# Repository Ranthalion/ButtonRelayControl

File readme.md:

# Button Relay Control

Controls 2 relays based on liquid level sensors and push buttons

Video demo and more images at https://imgur.com/a/c6JBYJK

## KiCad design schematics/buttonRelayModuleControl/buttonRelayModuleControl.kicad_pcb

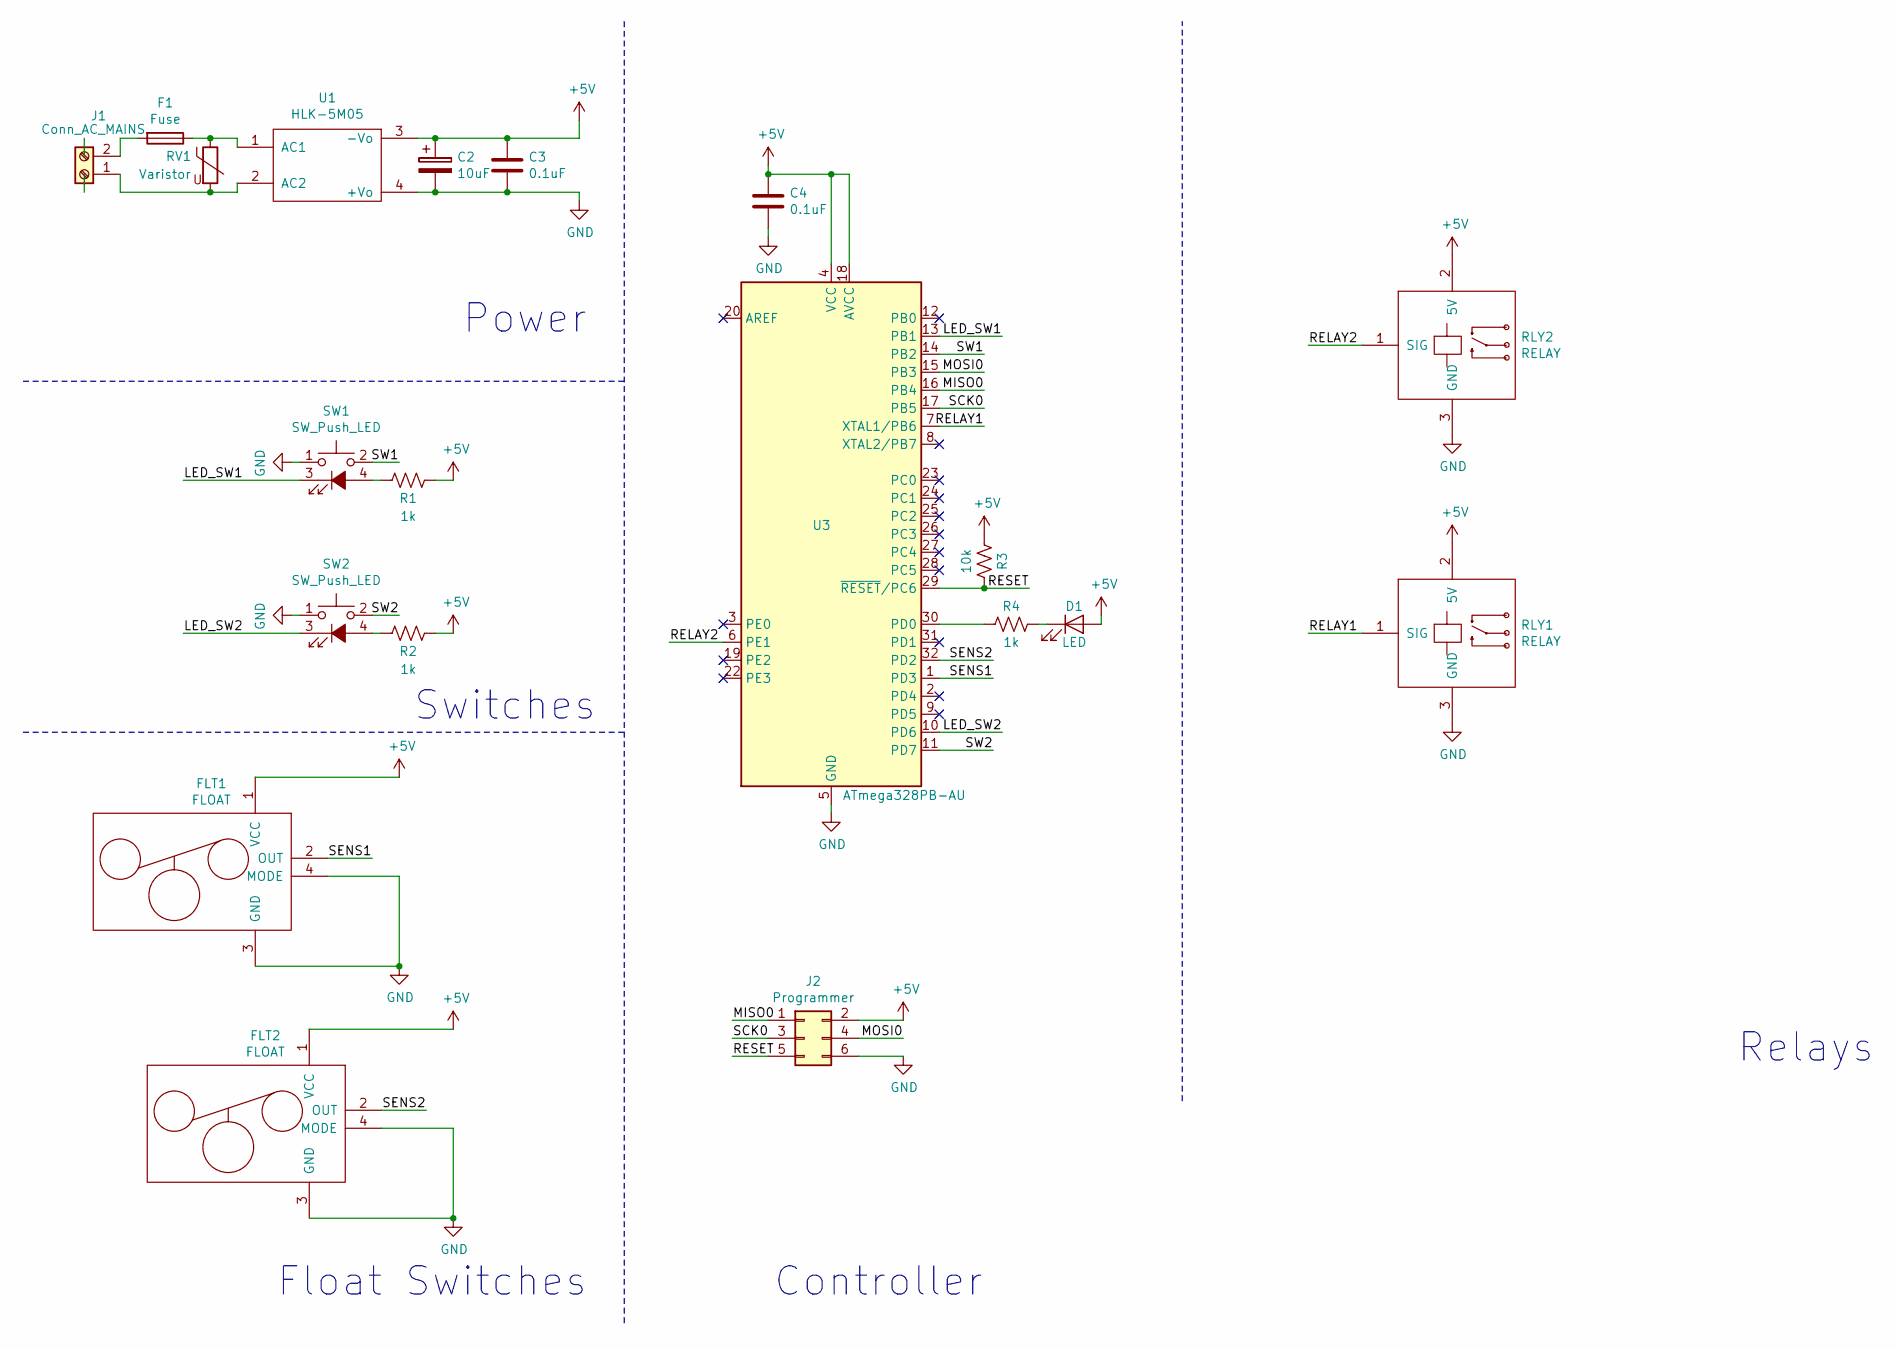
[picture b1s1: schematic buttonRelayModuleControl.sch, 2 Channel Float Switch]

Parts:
C2: 10uF; CP_Radial_D4.0mm_P1.50mm
C3, C4: 0.1uF; C_1206_3216Metric_Pad1.42x1.75mm_HandSolder
D1: LED; LED_0603_1608Metric_Pad1.05x0.95mm_HandSolder
F1: Fuse; Fuse_Bourns_MF-RG300; Part No 0466.125NR
FLT1, FLT2: FLOAT; JST_XH_B04B-XH-A_1x04_P2.50mm_Vertical
J1: Conn_AC_MAINS; Molex_Mega-Fit_76829-0102_2x01_P5.70mm_Vertical
J2: Programmer; PinHeader_2x03_P2.54mm_Vertical_SMD
R1, R2, R4: 1k; R_0805_2012Metric_Pad1.15x1.40mm_HandSolder
R3: 10k; R_1206_3216Metric_Pad1.42x1.75mm_HandSolder
RLY1, RLY2: RELAY; JST_XH_B03B-XH-A_1x03_P2.50mm_Vertical
RV1: Varistor; RV_Disc_D7mm_W3.4mm_P5mm; Part No ERZ-V14D241
SW1, SW2: SW_Push_LED; JST_XH_B04B-XH-A_1x04_P2.50mm_Vertical
U1: HLK-5M05
U3: ATmega328PB-AU; TQFP-32_7x7mm_P0.8mm

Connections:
+5V: C2.1, C3.1, C4.1, D1.2 (A), FLT1.1 (VCC), FLT2.1 (VCC), J2.2, R1.1, R2.1, R3.2, RLY1.2 (5V), RLY2.2 (5V), U1.3 (-Vo), U3.4 (VCC), U3.18 (AVCC)
/LED_SW1: SW1.3 (K), U3.13 (PB1)
/LED_SW2: SW2.3 (K), U3.10 (PD6)
/MISO0: J2.1, U3.16 (PB4)
/MOSI0: J2.4, U3.15 (PB3)
/RELAY1: RLY1.1 (SIG), U3.7 (XTAL1/PB6)
/RELAY2: RLY2.1 (SIG), U3.6 (PE1)
/RESET: J2.5, R3.1, U3.29 (~RESET~/PC6)
/SCK0: J2.3, U3.17 (PB5)
/SENS1: FLT1.2 (OUT), U3.1 (PD3)
/SENS2: FLT2.2 (OUT), U3.32 (PD2)
/SW1: SW1.2, U3.14 (PB2)
/SW2: SW2.2, U3.11 (PD7)
GND: C2.2, C3.2, C4.2, FLT1.3 (GND), FLT1.4 (MODE), FLT2.3 (GND), FLT2.4 (MODE), J2.6, RLY1.3 (GND), RLY2.3 (GND), SW1.1, SW2.1, U1.4 (+Vo), U3.5 (GND), U3.21 (GND)
unnamed: D1.1 (K), R4.1
unnamed: F1.1, RV1.1, U1.1 (AC1)
unnamed: F1.2, J1.2
unnamed: J1.1, RV1.2, U1.2 (AC2)
unnamed: R1.2, SW1.4 (A)
unnamed: R2.2, SW2.4 (A)
unnamed: R4.2, U3.30 (PD0)

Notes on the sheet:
Power
Switches
Float Switches
Relays
Controller

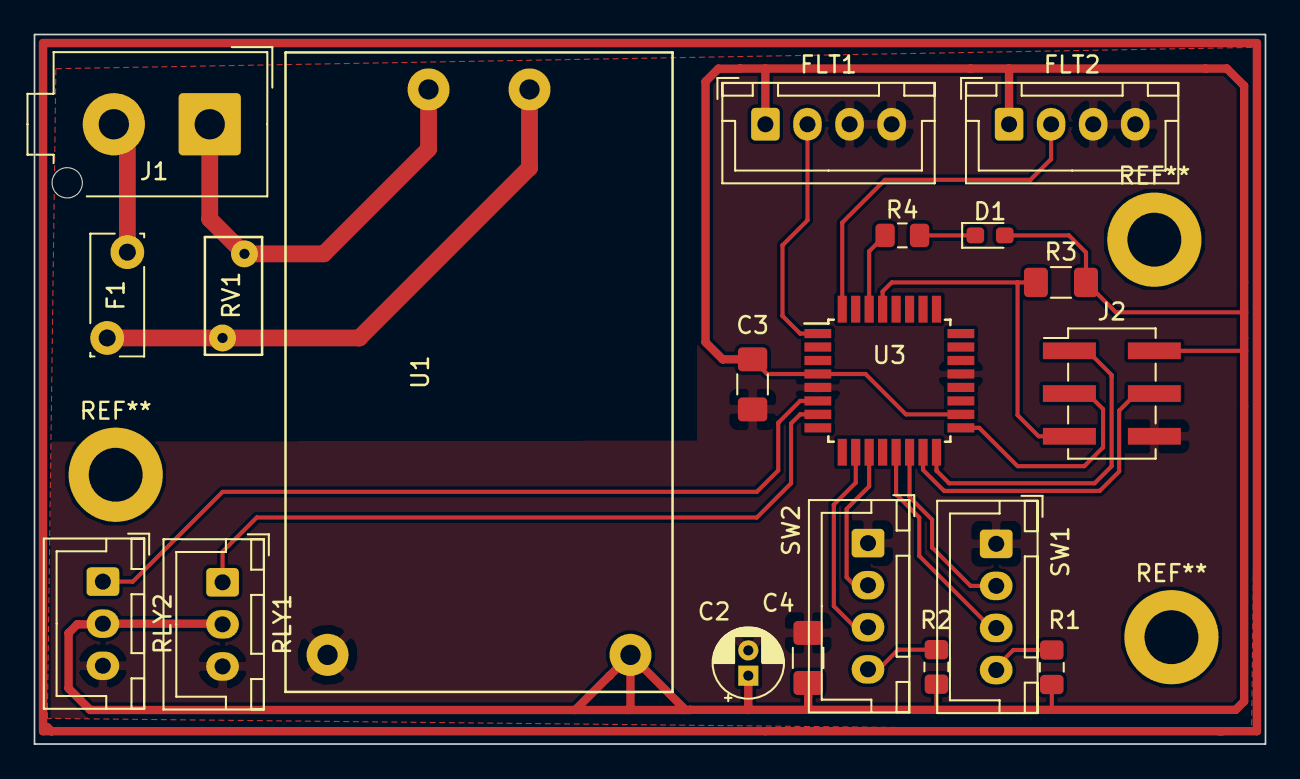
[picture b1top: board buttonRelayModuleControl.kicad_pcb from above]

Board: 2 copper layers, 73.2 x 42.2 mm, 20 parts (0 on the bottom side), 21 nets.

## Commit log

2018-10-21 Schematic and board layout
2018-10-22 Initial Firmware
2018-10-23 Hello World firmware
2018-10-23 update gitignore
2018-10-23 removing build files
2018-10-23 Enable pin change interrupts
2018-10-23 Timer setup
2018-10-24 LED Animation
2018-10-24 Add board layout image
2018-10-24 add missing image
2018-10-26 Button interrupts and button LED flash
2018-10-26 Implement state machines and activate relays
2018-10-26 Add level sensor to complete core functionality
2018-10-26 Sleep mode
2018-10-27 Add video an d image link to readme
2018-10-27 Add logo to board
2018-10-29 bug fix
